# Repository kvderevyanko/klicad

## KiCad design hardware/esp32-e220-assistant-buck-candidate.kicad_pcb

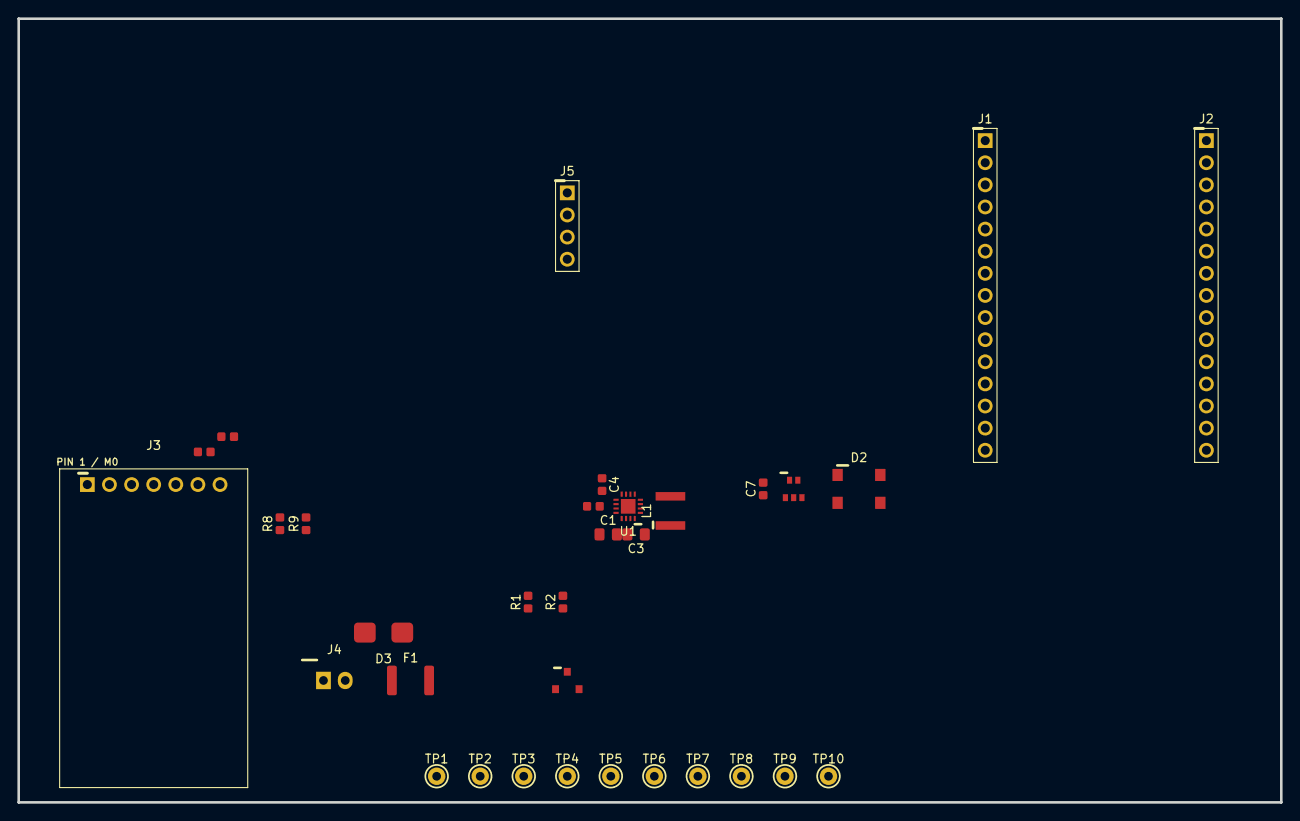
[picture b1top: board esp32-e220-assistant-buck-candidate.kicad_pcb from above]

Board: 2 copper layers, 145.0 x 90.0 mm, 33 parts (0 on the bottom side), 18 nets, no tracks yet.

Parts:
C1: GRM21BR61E106KA73; Murata_GRM21_2012Metric
C2, C6, C7: GRM188R71C104KA01D; Murata_GRM188_1608Metric
C3: GRM21BR61A226ME44; Murata_GRM21_2012Metric
C4: GRM1885C1H332JA01D; Murata_GRM188_1608Metric
C5: GRM188R61A106MAAL; Murata_GRM188_1608Metric
D2: WS2812B-V5; WorldSemi_WS2812B-V5_PLACEMENT_CANDIDATE_NOT_RELEASED
D3: SMBJ10CA; Littelfuse_SMBJ10CA_DO214AA
F1: 1812L200/16; Littelfuse_1812L200_16_4532Metric
J1: SSW-115-02-G-S DEVKIT LEFT; Samtec_SSW_1x15_P2.54mm_THT
J2: SSW-115-02-G-S DEVKIT RIGHT; Samtec_SSW_1x15_P2.54mm_THT
J3: E220-400T22D / E220-900T22D SOCKET; E220_T22D_Socket_400_900
J4: B2B-XH-A; JST_B2B-XH-A_1x02_P2.50mm_THT
J5: SSW-104-02-G-S; Samtec_SSW_1x04_P2.54mm_THT
L1: XFL4020-222MEB; Coilcraft_XFL4020-222MEB
Q1: DMP3130LQ-7; Diodes_DMP3130LQ-7_SOT23
R1: 100k 1%; Resistor_0603_1608Metric
R2: 1M 1%; Resistor_0603_1608Metric
R8, R9: 10k 1%; Resistor_0603_1608Metric
TP1: BAT_PLUS; TestPoint_THT_1p0mm_PROTOTYPE
TP2: GND; TestPoint_THT_1p0mm_PROTOTYPE
TP3: BUCK_IN; TestPoint_THT_1p0mm_PROTOTYPE
TP4, TP5: 5V_SYS; TestPoint_THT_1p0mm_PROTOTYPE
TP6: E220_M0; TestPoint_THT_1p0mm_PROTOTYPE
TP7: E220_M1; TestPoint_THT_1p0mm_PROTOTYPE
TP8: E220_AUX; TestPoint_THT_1p0mm_PROTOTYPE
TP9: E220_RXD; TestPoint_THT_1p0mm_PROTOTYPE
TP10: E220_TXD; TestPoint_THT_1p0mm_PROTOTYPE
U1: TPS62133RGT; TI_TPS62133RGT_RGT0016C
U3: SN74AHCT1G125DBVR; TI_SN74AHCT1G125DBVR_SOT23-5

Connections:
/5V_SYS: C3.1, C5.1, C6.1, C7.1, D2.1, J1.1, J3.6, L1.2, TP4.1, TP5.1, U1.7, U1.14, U3.5
/BAT_FUSED: D3.1, F1.2, Q1.3
/BAT_PLUS: F1.1, J4.1, TP1.1
/BUCK_IN: C1.1, C2.1, Q1.2, R2.1, TP3.1, U1.10, U1.11, U1.12, U1.13
/BUCK_SW: L1.1, U1.1, U1.2, U1.3
/DEVKIT_3V3: J2.1, J5.2
/E220_AUX: J1.6, J3.5, TP8.1
/E220_M0: J1.8, J3.1, R8.1, TP6.1
/E220_M1: J1.7, J3.2, R9.1, TP7.1
/E220_RXD: J2.7, J3.3, TP9.1
/E220_TXD: J2.6, J3.4, TP10.1
/GND: C1.2, C2.2, C3.2, C4.2, C5.2, C6.2, C7.2, D2.3, D3.2, J1.2, J2.2, J3.7, J4.2, J5.1, R1.2, R8.2, R9.2, TP2.1, U1.5, U1.6, U1.8, U1.15, U1.16, U1.EP, U3.1, U3.3
/OLED_SCL: J2.14, J5.3
/OLED_SDA: J2.11, J5.4
/Q1_GATE: Q1.1, R1.1, R2.2
/SS_TR: C4.1, U1.9
/WS2812_DATA_3V3: J2.5, U3.2
/WS2812_DIN: D2.4, U3.4

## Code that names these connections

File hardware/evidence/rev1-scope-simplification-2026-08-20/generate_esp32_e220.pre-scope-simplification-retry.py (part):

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battery = [("1","BAT+","passive"),("2","BAT-","passive")]
user_gpio = [("1","GND"),("2","GPIO13"),("3","GND"),("4","GPIO14"),("5","GND"),
             ("6","GPIO18"),("7","GND"),("8","GPIO19"),("9","AUX_3V3"),("10","GPIO23")]
display_aux = [("1","GND"),("2","AUX_3V3"),("3","GPIO21 / OLED_SDA"),("4","GPIO22 / OLED_SCL"),
               ("5","GPIO18"),("6","GPIO23"),("7","GPIO19"),("8","GPIO13"),("9","GPIO14"),
               ("10","GPIO33"),("11","GND"),("12","AUX_3V3")]
power_switch = [("1","BAT_FUSED"),("2","BAT_SW")]
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    items.append(instance(a,b,c,d,e,f,dnp=b in {"R10", "R11"}))

# Verified DevKit/E220/LED signals retained from Stage 5 plus authorized Rev.1 expansion.
for n, net in [(1,"DEVKIT_VIN"),(2,"GND"),(3,"GPIO13"),(5,"GPIO14"),(6,"E220_AUX"),(7,"E220_M1"),(8,"E220_M0"),
               (9,"GPIO33"),(10,"BAT_SENSE")]:
    items.append(pin_label(70,100,len(left),n,net))
for n in set(range(1,16)) - {1,2,3,5,6,7,8,9,10}: items.append(pin_no_connect(70,100,len(left),n))
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    items.append(pin_label(115,100,len(right),n,net))
# One-sheet I2C nets: local labels intentionally connect DevKit, socket and
# optional pull-up sites without creating a global-label/local-label ERC mix.
items += [label("OLED_SDA", *pin_pos(115,100,len(right),11)), label("OLED_SCL", *pin_pos(115,100,len(right),14))]
for n in set(range(1,16)) - {1,2,5,6,7,9,10,11,14,15}: items.append(pin_no_connect(115,100,len(right),n))
for n, net in [(1,"E220_M0"),(2,"E220_M1"),(3,"E220_RXD"),(4,"E220_TXD"),(5,"E220_AUX"),(6,"5V_SYS"),(7,"GND")]:
    items.append(pin_label(175,105,len(e220),n,net))
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    items.append(pin_label(330,175,len(oled_i2c),n,net))

# Battery connector, switch and protection: the P-MOS body diode must precharge from
# BAT_SW (D, pin 3) to BUCK_IN (S, pin 2). Correct polarity then produces
# negative VGS and enhanced conduction; reversed pack polarity leaves the body
# diode reverse-biased and VGS non-negative. D3 is across BAT_FUSED/GND.
items += [pin_label(25,155,len(battery),1,"BAT_PLUS"), pin_label(25,155,len(battery),2,"GND"),
          pin_label(45,155,len(fuse),1,"BAT_PLUS"), pin_label(45,155,len(fuse),2,"BAT_FUSED"),
          pin_label(65,165,len(tvs),1,"BAT_FUSED"), pin_label(65,165,len(tvs),2,"GND"),
          pin_label(85,170,len(power_switch),1,"BAT_FUSED"), pin_label(85,170,len(power_switch),2,"BAT_SW"),
          pin_label(85,155,len(pmos),1,"Q1_GATE"), pin_label(85,155,len(pmos),2,"BUCK_IN"), pin_label(85,155,len(pmos),3,"BAT_SW")]

# DEVKIT_PWR intentionally creates two separate nets: a removable shunt is the
# only approved connection from 5V_SYS to the DevKit VIN pad.
items += [pin_label(85,70,len(devkit_pwr),1,"5V_SYS"), pin_label(85,70,len(devkit_pwr),2,"DEVKIT_VIN")]

# BAT_SENSE is a strictly local divider from BUCK_IN to ADC1 GPIO32.  C8 is the
# Espressif-recommended 100-nF ADC-input filter capacitor.
items += [pin_label(80,255,2,1,"BUCK_IN"), pin_label(80,255,2,2,"BAT_SENSE"),
          pin_label(100,255,2,1,"BAT_SENSE"), pin_label(100,255,2,2,"GND"),
          pin_label(120,255,2,1,"BAT_SENSE"), pin_label(120,255,2,2,"GND")]

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# series component or alternate signal identity is introduced by this stage.
for n, net in [(1,"GND"),(2,"GPIO13"),(3,"GND"),(4,"GPIO14"),(5,"GND"),(6,"GPIO18"),(7,"GND"),(8,"GPIO19"),(9,"AUX_3V3"),(10,"GPIO23")]:
    items.append(pin_label(235,170,len(user_gpio),n,net))
for n, net in [(1,"GND"),(2,"AUX_3V3"),(3,"OLED_SDA"),(4,"OLED_SCL"),(5,"GPIO18"),(6,"GPIO23"),
               (7,"GPIO19"),(8,"GPIO13"),(9,"GPIO14"),(10,"GPIO33"),(11,"GND"),(12,"AUX_3V3")]:
    items.append(pin_label(235,210,len(display_aux),n,net))

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               (13,"BUCK_IN"),(14,"5V_SYS"),(15,"GND"),(16,"GND"),(17,"GND")]:
    items.append(pin_label(130,180,len(tps62133),n,net))
items.append(pin_no_connect(130,180,len(tps62133),4))
items += [pin_label(185,180,len(inductor),1,"BUCK_SW"), pin_label(185,180,len(inductor),2,"5V_SYS")]

for n, net in [(1,"GND"),(2,"WS2812_DATA_3V3"),(3,"GND"),(4,"WS2812_DIN"),(5,"5V_SYS")]: items.append(pin_label(275,105,len(ahct),n,net))
for n, net in [(1,"5V_SYS"),(3,"GND"),(4,"WS2812_DIN")]: items.append(pin_label(325,105,len(ws2812),n,net))
items.append(pin_no_connect(325,105,len(ws2812),2))

# U4 is the only authorized source of AUX_3V3.  The DCY tab is electrically
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          pin_label(315,255,2,1,"AUX_3V3"), pin_label(315,255,2,2,"GND")]

for ref, x, y, net in [("TP1",25,230,"BAT_PLUS"),("TP2",45,230,"GND"),("TP3",65,230,"BUCK_IN"),("TP4",85,230,"5V_SYS"),("TP5",105,230,"5V_SYS"),
                       ("TP6",25,240,"E220_M0"),("TP7",45,240,"E220_M1"),("TP8",65,240,"E220_AUX"),("TP9",85,240,"E220_RXD"),("TP10",105,240,"E220_TXD")]: items.append(label(net,x,y))

# ERC source markers: external protected battery/return plus the explicitly
# declared protected BUCK_IN and U1-generated 5V_SYS domains.
items += [label("BAT_PLUS",35,175), label("GND",35,185), label("BUCK_IN",35,195), label("5V_SYS",35,205), label("DEVKIT_3V3",35,215)]

for x,y,a,b in [(65,180,"Q1_GATE","GND"),(85,180,"BUCK_IN","Q1_GATE"),(105,205,"BUCK_IN","GND"),(125,205,"BUCK_IN","GND"),
                (145,205,"SS_TR","GND"),(185,205,"5V_SYS","GND"),(175,140,"5V_SYS","GND"),(195,140,"5V_SYS","GND"),
                (215,140,"E220_M0","GND"),(235,140,"E220_M1","GND"),(285,140,"5V_SYS","GND"),
                (300,185,"OLED_SDA","AUX_3V3"),(320,185,"OLED_SCL","AUX_3V3")]: items += [pin_label(x,y,2,1,a),pin_label(x,y,2,2,b)]

items += [
    # Functional-block headers deliberately contain the operational information
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    note("Inter-block links use net labels.  Local wires show the active power, bypass and interface support networks.", 18, 39),
    heading("G. USER EXPANSION", 215, 145),
    note("J6 USER_GPIO: 1 GND 2 GPIO13 3 GND 4 GPIO14 5 GND 6 GPIO18 7 GND 8 GPIO19 9 AUX_3V3 10 GPIO23", 215, 150),
    note("J7 DISPLAY_AUX: 1 GND 2 AUX_3V3 3 GPIO21/OLED_SDA 4 GPIO22/OLED_SCL 5 GPIO18 6 GPIO23 7 GPIO19 8 GPIO13 9 GPIO14 10 GPIO33 11 GND 12 AUX_3V3", 215, 155),
    note("J6/J7: user-install headers, PCBA DNP.  Direct nets only; no series/inline conditioning in this revision.", 215, 160),
    note("JP1 DEVKIT_PWR: 5V_SYS -> JP1.1 -> removable shunt -> JP1.2 -> DEVKIT_VIN -> J1.1", 18, 205),
    note("BAT+ -> F1 -> BAT_FUSED -> J8.1 -> EXTERNAL MECHANICAL SWITCH -> J8.2 -> BAT_SW -> Q1.3 -> BUCK_IN", 18, 210),
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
